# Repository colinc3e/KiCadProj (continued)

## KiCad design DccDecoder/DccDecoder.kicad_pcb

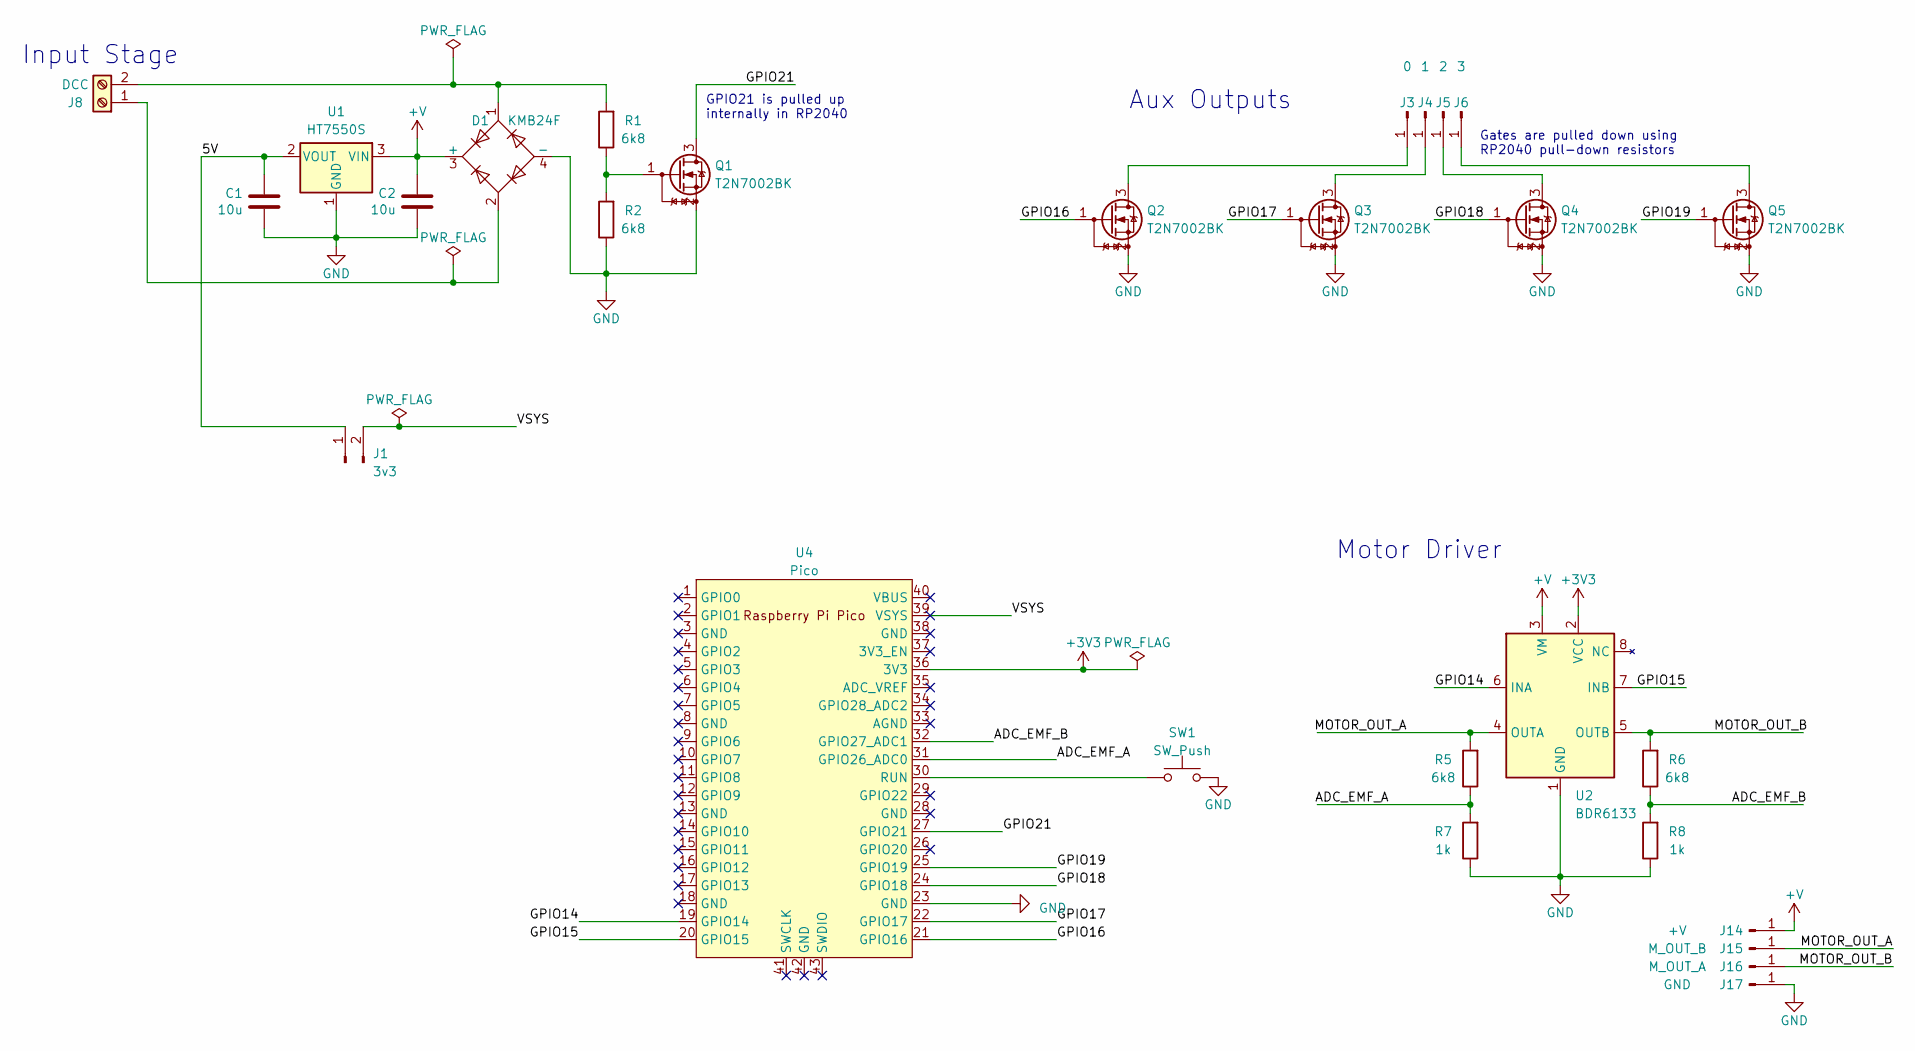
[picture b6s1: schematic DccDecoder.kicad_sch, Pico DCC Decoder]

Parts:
C1, C2: 10u; C_1206_3216Metric_Pad1.33x1.80mm_HandSolder
D1: KMB24F; TO-269AA
J1: 3v3; PinHeader_1x02_P2.54mm_Vertical
J3: 0; TestPoint_Pad_D2.0mm
J4: 1; TestPoint_Pad_D2.0mm
J5: 2; TestPoint_Pad_D2.0mm
J6: 3; TestPoint_Pad_D2.0mm
J8: DCC; TerminalBlock_Phoenix_PT-1,5-2-3.5-H_1x02_P3.50mm_Horizontal
J14: +V; TestPoint_Pad_D2.0mm
J15: M_OUT_B; TestPoint_Pad_D2.0mm
J16: M_OUT_A; TestPoint_Pad_D2.0mm
J17: GND; TestPoint_Pad_D2.0mm
Q1, Q2, Q3, Q4, Q5: T2N7002BK; SOT-23
R1, R2, R5, R6: 6k8; R_1206_3216Metric_Pad1.30x1.75mm_HandSolder
R7, R8: 1k; R_1206_3216Metric_Pad1.30x1.75mm_HandSolder
SW1: SW_Push; SW_Tactile_SPST_NO_Straight_CK_PTS636Sx25SMTRLFS
U1: HT7550S; SOT-23
U2: BDR6133; SOIC-8-1EP_3.9x4.9mm_P1.27mm_EP2.41x3.3mm_ThermalVias
U4: Pico; RP2040Pico

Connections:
+3V3: U2.2 (VCC), U4.36 (3V3)
+V: C2.1, D1.3 (+), J14.1, U1.3 (VIN), U2.3 (VM)
/5V: C1.1, J1.1, U1.2 (VOUT)
/ADC_EMF_A: R5.1, R7.2, U4.31 (GPIO26_ADC0)
/ADC_EMF_B: R6.1, R8.2, U4.32 (GPIO27_ADC1)
/GPIO14: U2.6 (INA), U4.19 (GPIO14)
/GPIO15: U2.7 (INB), U4.20 (GPIO15)
/GPIO16: Q2.1 (G), U4.21 (GPIO16)
/GPIO17: Q3.1 (G), U4.22 (GPIO17)
/GPIO18: Q4.1 (G), U4.24 (GPIO18)
/GPIO19: Q5.1 (G), U4.25 (GPIO19)
/GPIO21: Q1.3 (D), U4.27 (GPIO21)
/MOTOR_OUT_A: J15.1, R5.2, U2.4 (OUTA)
/MOTOR_OUT_B: J16.1, R6.2, U2.5 (OUTB)
/VSYS: J1.2, U4.39 (VSYS)
GND: C1.2, C2.2, D1.4 (-), J17.1, Q1.2 (S), Q2.2 (S), Q3.2 (S), Q4.2 (S), Q5.2 (S), R2.1, R7.1, R8.1, SW1.2, U1.1 (GND), U2.1 (GND), U2.9 (GND), U4.23 (GND)
unnamed: J3.1, Q2.3 (D)
unnamed: J4.1, Q3.3 (D)
unnamed: J5.1, Q4.3 (D)
unnamed: J6.1, Q5.3 (D)
unnamed: D1.2, J8.1
unnamed: D1.1, J8.2, R1.2
unnamed: Q1.1 (G), R1.1, R2.2
unnamed: SW1.1, U4.30 (RUN)

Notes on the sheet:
Gates are pulled down using RP2040 pull-down resistors
Motor Driver
GPIO21 is pulled up internally in RP2040
Aux Outputs
Input Stage

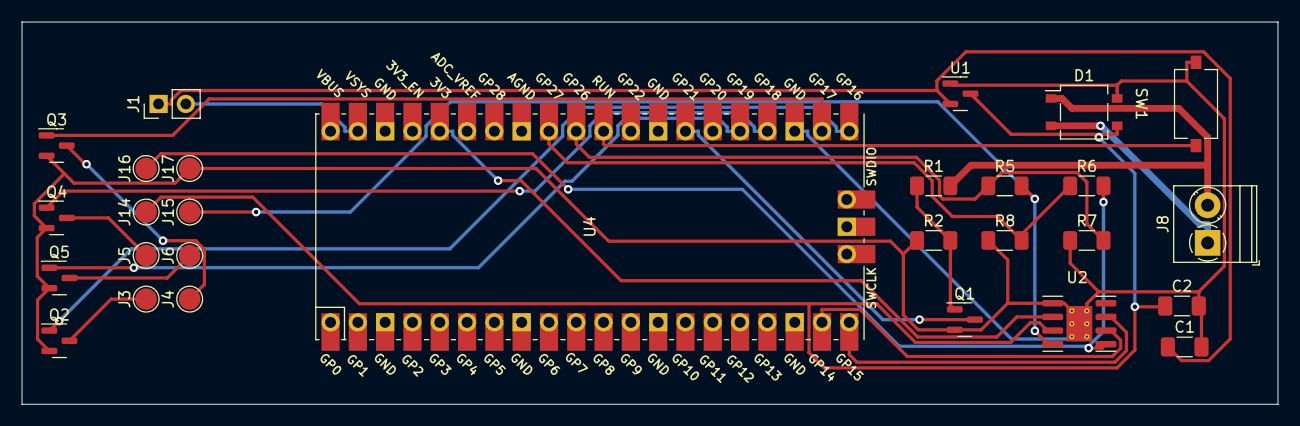
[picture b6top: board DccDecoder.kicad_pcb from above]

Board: 2 copper layers, 116.8 x 35.6 mm, 28 parts (0 on the bottom side), 24 nets.

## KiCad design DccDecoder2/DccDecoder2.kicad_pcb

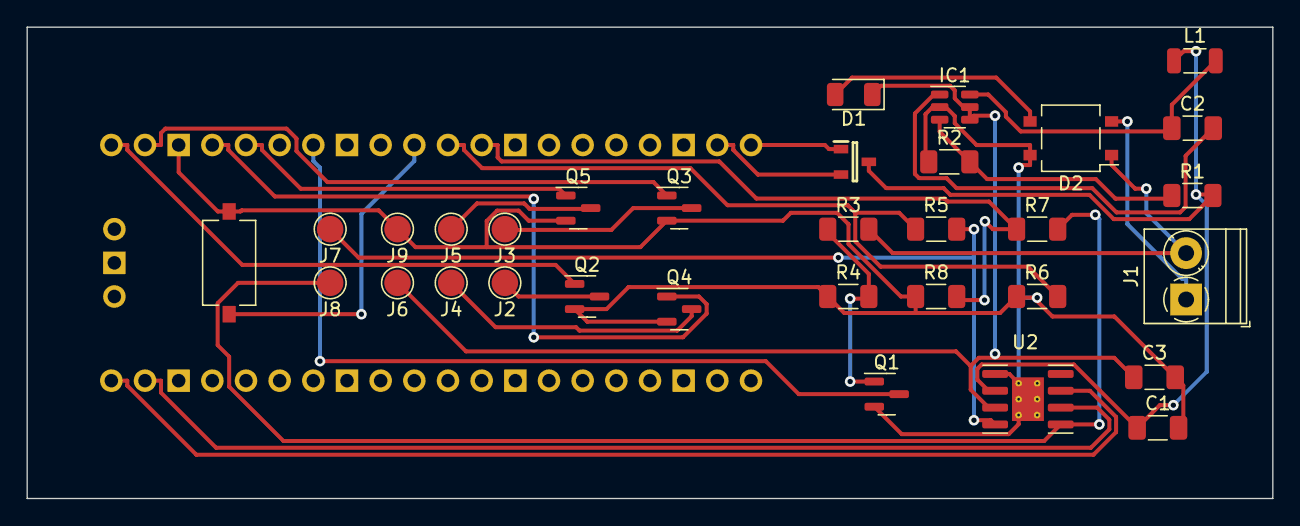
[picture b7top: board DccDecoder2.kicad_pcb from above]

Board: 2 copper layers, 94.0 x 35.6 mm, 33 parts (1 on the bottom side), 27 nets.

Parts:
C1: 10u; C_1206_3216Metric_Pad1.33x1.80mm_HandSolder
C2: 100n; C_1206_3216Metric_Pad1.33x1.80mm_HandSolder
C3: 2.2uF/25V; C_1206_3216Metric_Pad1.33x1.80mm_HandSolder
D1: CUHS20F30; D_1206_3216Metric
D2: KMB24F; TO-269AA
IC1: AP64060QWU-7; TSOT-23-6
J1: DCC; TerminalBlock_Phoenix_PT-1,5-2-3.5-H_1x02_P3.50mm_Horizontal
J2: 0; TestPoint_Pad_D2.0mm
J3: 1; TestPoint_Pad_D2.0mm
J4: 2; TestPoint_Pad_D2.0mm
J5: 3; TestPoint_Pad_D2.0mm
J6: +V; TestPoint_Pad_D2.0mm
J7: M_OUT_B; TestPoint_Pad_D2.0mm
J8: M_OUT_A; TestPoint_Pad_D2.0mm
J9: GND; TestPoint_Pad_D2.0mm
L1: 10uH; L_1206_3216Metric
Q1, Q2, Q3, Q4, Q5: T2N7002BK; SOT-23
Q6: DMG2305UX-7; SOT96P240X110-3N
R1: 69k8; R_1206_3216Metric_Pad1.30x1.75mm_HandSolder
R2: 22k1; R_1206_3216Metric_Pad1.30x1.75mm_HandSolder
R3, R4, R5, R7: 6k8; R_1206_3216Metric_Pad1.30x1.75mm_HandSolder
R6, R8: 1k; R_1206_3216Metric_Pad1.30x1.75mm_HandSolder
SW1: SW_Push; SW_Tactile_SPST_NO_Straight_CK_PTS636Sx25SMTRLFS
U1: Pico; RP2040Pico
U2: BDR6133; SOIC-8-1EP_3.9x4.9mm_P1.27mm_EP2.41x3.3mm_ThermalVias

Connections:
+3V3: C1.1, L1.1, Q6.3, R1.2, U2.2 (VCC)
+V: C3.1, D1.1 (K), IC1.4 (EN), IC1.5 (VIN), J6.1, U2.3 (VM)
/ADC_EMF_A: R5.1, R6.2, U1.31 (GPIO26_ADC0)
/ADC_EMF_B: R7.1, R8.2, U1.32 (GPIO27_ADC1)
/GPIO14: U1.19 (GPIO14), U2.6 (INA)
/GPIO15: U1.20 (GPIO15), U2.7 (INB)
/GPIO16: Q2.1 (G), U1.21 (GPIO16)
/GPIO17: Q3.1 (G), U1.22 (GPIO17)
/GPIO18: Q4.1 (G), U1.24 (GPIO18)
/GPIO19: Q5.1 (G), U1.25 (GPIO19)
/GPIO21: Q1.3 (D), U1.27 (GPIO21)
/MOTOR_OUT_A: J7.1, R5.2, U2.4 (OUTA)
/MOTOR_OUT_B: J8.1, R7.2, U2.5 (OUTB)
/VSYS: Q6.2, U1.39 (VSYS)
GND: C1.2, C3.2, D2.4 (-), IC1.2 (GND), J9.1, Q1.2 (S), Q2.2 (S), Q3.2 (S), Q4.2 (S), Q5.2 (S), R2.1, R4.1, R6.1, R8.1, SW1.2, U1.23 (GND), U2.1 (GND), U2.9 (GND)
unnamed: D1.2 (A), D2.3 (+)
unnamed: C2.2, IC1.1 (BST)
unnamed: IC1.3 (FB), R1.1, R2.2
unnamed: C2.1, IC1.6 (SW), L1.2
unnamed: D2.2, J1.1
unnamed: D2.1, J1.2, R3.2
unnamed: J2.1, Q2.3 (D)
unnamed: J3.1, Q3.3 (D)
unnamed: J4.1, Q4.3 (D)
unnamed: J5.1, Q5.3 (D)
unnamed: Q1.1 (G), R3.1, R4.2
unnamed: SW1.1, U1.30 (RUN)

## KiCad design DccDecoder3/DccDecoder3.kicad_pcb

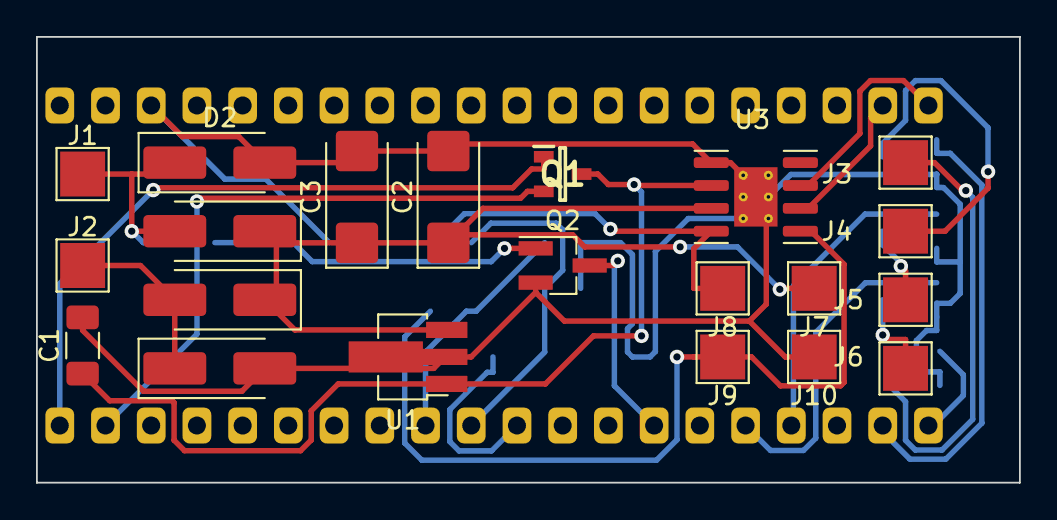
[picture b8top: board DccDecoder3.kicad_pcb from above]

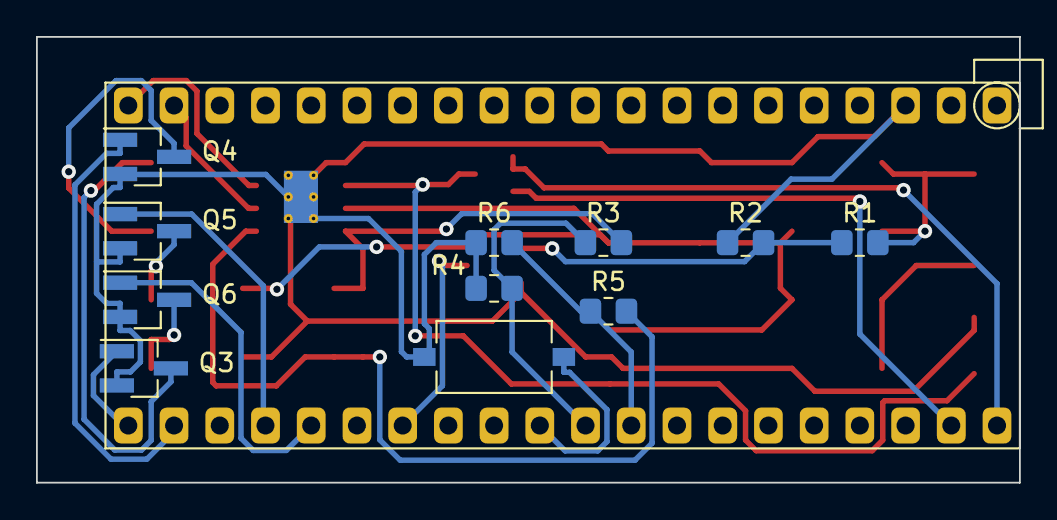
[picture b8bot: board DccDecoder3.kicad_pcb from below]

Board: 2 copper layers, 54.6 x 24.8 mm, 33 parts (12 on the bottom side), 24 nets.

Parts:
C1: 10uf/16V; C_1206_3216Metric_Pad1.33x1.80mm_HandSolder
C2: 10uF/25V; CP_EIA-6032-20_AVX-F_Pad2.25x2.35mm_HandSolder
C3: 10uF/25v; CP_EIA-6032-20_AVX-F_Pad2.25x2.35mm_HandSolder
D1, D2, D3, D4: RBR3L60AD; D_SMA_Handsoldering
J1, J2: PAD; TestPoint_Pad_2.5x2.5mm
J3: 0; TestPoint_Pad_2.5x2.5mm
J4: 1; TestPoint_Pad_2.5x2.5mm
J5: 2; TestPoint_Pad_2.5x2.5mm
J6: 3; TestPoint_Pad_2.5x2.5mm
J7: +V; TestPoint_Pad_2.5x2.5mm
J8: M_OUT_B; TestPoint_Pad_2.5x2.5mm
J9: M_OUT_A; TestPoint_Pad_2.5x2.5mm
J10: GND; TestPoint_Pad_2.5x2.5mm
Q1: DMG2305UX-7; SOT96P240X110-3N
Q2, Q3, Q4, Q5, Q6: 2N7002K; SOT-23_Handsoldering
R1, R2, R3, R5: 6k8; R_0805_2012Metric_Pad1.20x1.40mm_HandSolder
R4, R6: 1k; R_0805_2012Metric_Pad1.20x1.40mm_HandSolder
SW1: SW_Push; SW_Tactile_SPST_NO_Straight_CK_PTS636Sx25SMTRLFS
U1: AP7384-33Y; SOT-89-3_Handsoldering
U2: Pico_RaspberryPico; RaspberryPico_TH_NoSWD
U3: BDR6133; SOIC-8-1EP_3.9x4.9mm_P1.27mm_EP2.41x3.3mm_ThermalVias

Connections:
+3V3: C1.1, Q1.3, U1.1 (VO), U3.2 (VCC)
+V: C2.1, C3.1, D1.1 (K), D4.1 (K), J7.1, U1.3 (VI), U3.3 (VM)
/ADC_EMF_A: R3.1, R4.2, U2.31 (GPIO26)
/ADC_EMF_B: R5.1, R6.2, U2.32 (GPIO27)
/GPIO14: U2.19 (GPIO14), U3.6 (INA)
/GPIO15: U2.20 (GPIO15), U3.7 (INB)
/GPIO16: Q3.1 (G), U2.21 (GPIO16)
/GPIO17: Q4.1 (G), U2.22 (GPIO17)
/GPIO18: Q5.1 (G), U2.24 (GPIO18)
/GPIO19: Q6.1 (G), U2.25 (GPIO19)
/GPIO21: Q2.3 (D), U2.27 (GPIO21)
/MOTOR_OUT_A: J8.1, R3.2, U3.4 (OUTA)
/MOTOR_OUT_B: J9.1, R5.2, U3.5 (OUTB)
/VSYS: Q1.2, U2.39 (VSYS)
GND: C1.2, C2.2, C3.2, D2.2 (A), D3.2 (A), J10.1, Q2.2 (S), Q3.2 (S), Q4.2 (S), Q5.2 (S), Q6.2 (S), R2.1, R4.1, R6.1, SW1.2, U1.2 (GND), U2.3 (GND), U3.1 (GND), U3.9 (GND)
unnamed: D1.2 (A), D2.1 (K), J1.1, R1.2
unnamed: D3.1 (K), D4.2 (A), J2.1
unnamed: J3.1, Q3.3 (D)
unnamed: J4.1, Q4.3 (D)
unnamed: J5.1, Q5.3 (D)
unnamed: J6.1, Q6.3 (D)
unnamed: Q2.1 (G), R1.1, R2.2
unnamed: SW1.1, U2.30 (RUN)
unnamed: Q1.1, U2.40 (VBUS)
